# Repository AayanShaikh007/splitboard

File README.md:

# Splitboard
### A split keyboard modelled after the Ergodox with wireless connectivity

## What is the Splitboard?

The splitboard is a diy keyboard modelled after the Ergodox that has wireless bluetooth connectivity and on-board battery charging/management. The most striking thing about the keyboard is probably its distinct appearance compared to other keyboards, but hopefully this will add to the ergonomics of the keyboard. For this keyboard, I wanted to incorporate a number of features that I liked about my last keyboard, such as RGB lighting and Kalih hotswap sockets, while also adressing some of the issues with my last keyboard.

Typical Ergodox layout

## Why did I make the Splitboard?

I made the splitboard as a follow up to my original keyboard to address some mistakes I made in my last keyboard. Firstly, I made the case walls way too thick, at 1 cm, where in reality I only needed 2-4 mm. Additionally, I see now that the keyboard has a very large footprint on my desk and is difficult to move into a comfortable typing position. The splitboard consists of two, very portable halves that can be arranged around your desk in any way you want. Additionally, the case is much more asthetically appealing with low-profile walls (3mm) and a voronoi pattern on the bottom. Check out the product gallery to get a preview of the project.  

# Product Gallery

# BOM Table
| Item                        | Amount | Bought? | Cost (CAD) | Total Cost | Notes                                      | Link |
|-----------------------------|--------|---------|------------|-------------|---------------------------------------------|------|
| Adafruit Feather NRF52840   | 2      | n       | 37.79      | 75.58       |                                             | [AliExpress](https://www.aliexpress.com/item/1005009226053516.html?src=bing&aff_short_key=UneMJZVf&aff_platform=true&isdl=y&albch=shopping&acnt=135105396&albcp=555403205&albag=1301822986926870&slnk=&trgt=pla-2333163674559409&plac=&crea=81363996201255&netw=o&device=c&mtctp=e&utm_source=Bing&utm_medium=shopping&utm_campaign=PA_Bing_CA_PMAX_ALL_maxvalue_20250428_newstore_purchase&utm_content=%E9%87%8D%E5%A4%A7%E4%BB%B6&utm_term=Adafruit%20Feather%20nRF52840%20Express) |
| Switches (need 76)          | 1      | n       | 26.99      | 26.99       |                                             | [Amazon](https://www.amazon.ca/Kailh-Mechanical-Keyboard-Switches-Bronze/dp/B078872V4C) |
| Kalih Sockets               | 1      | n       | 13.57      | 13.57       |                                             | [AliExpress](https://www.aliexpress.com/item/1005007476614771.html) |
| Diodes                      | 1      | n       | 11.36      | 11.36       | Possibly cheaper if bought with other stuff | [AliExpress](https://www.aliexpress.com/item/4000142272546.html) |
| SK6812mini-e                | 1      | n       | 8.04       | 8.04        |                                             | [AliExpress](https://www.aliexpress.com/item/1005009217389452.html) |
| Keycaps                     | 1      | n       | 29.99      | 29.99       |                                             | [Amazon](https://www.amazon.ca/124-Key-Keycaps-Percent-Keyboard-Dye-Sub/dp/B09NRK5B3L) |
| PCB Manufacturing           | 2      | n       | 19.89      | 39.78       | $20 highway coupon (not applied)            | — |
| Stabilizers                 | 1      | n       | 7.29       | 7.29        |                                             | [AliExpress](https://www.aliexpress.com/item/1005009141481219.html) |

|               |        |         |        |         |             |             |
|---------------|--------|---------|--------|---------|-------------|-------------|
|               |        |         | **CAD** | **USD** |             |             |
| **Total Cost**|        |         | 212.60 | 155.20  | Note: 150 USD = 204.58 CAD | |

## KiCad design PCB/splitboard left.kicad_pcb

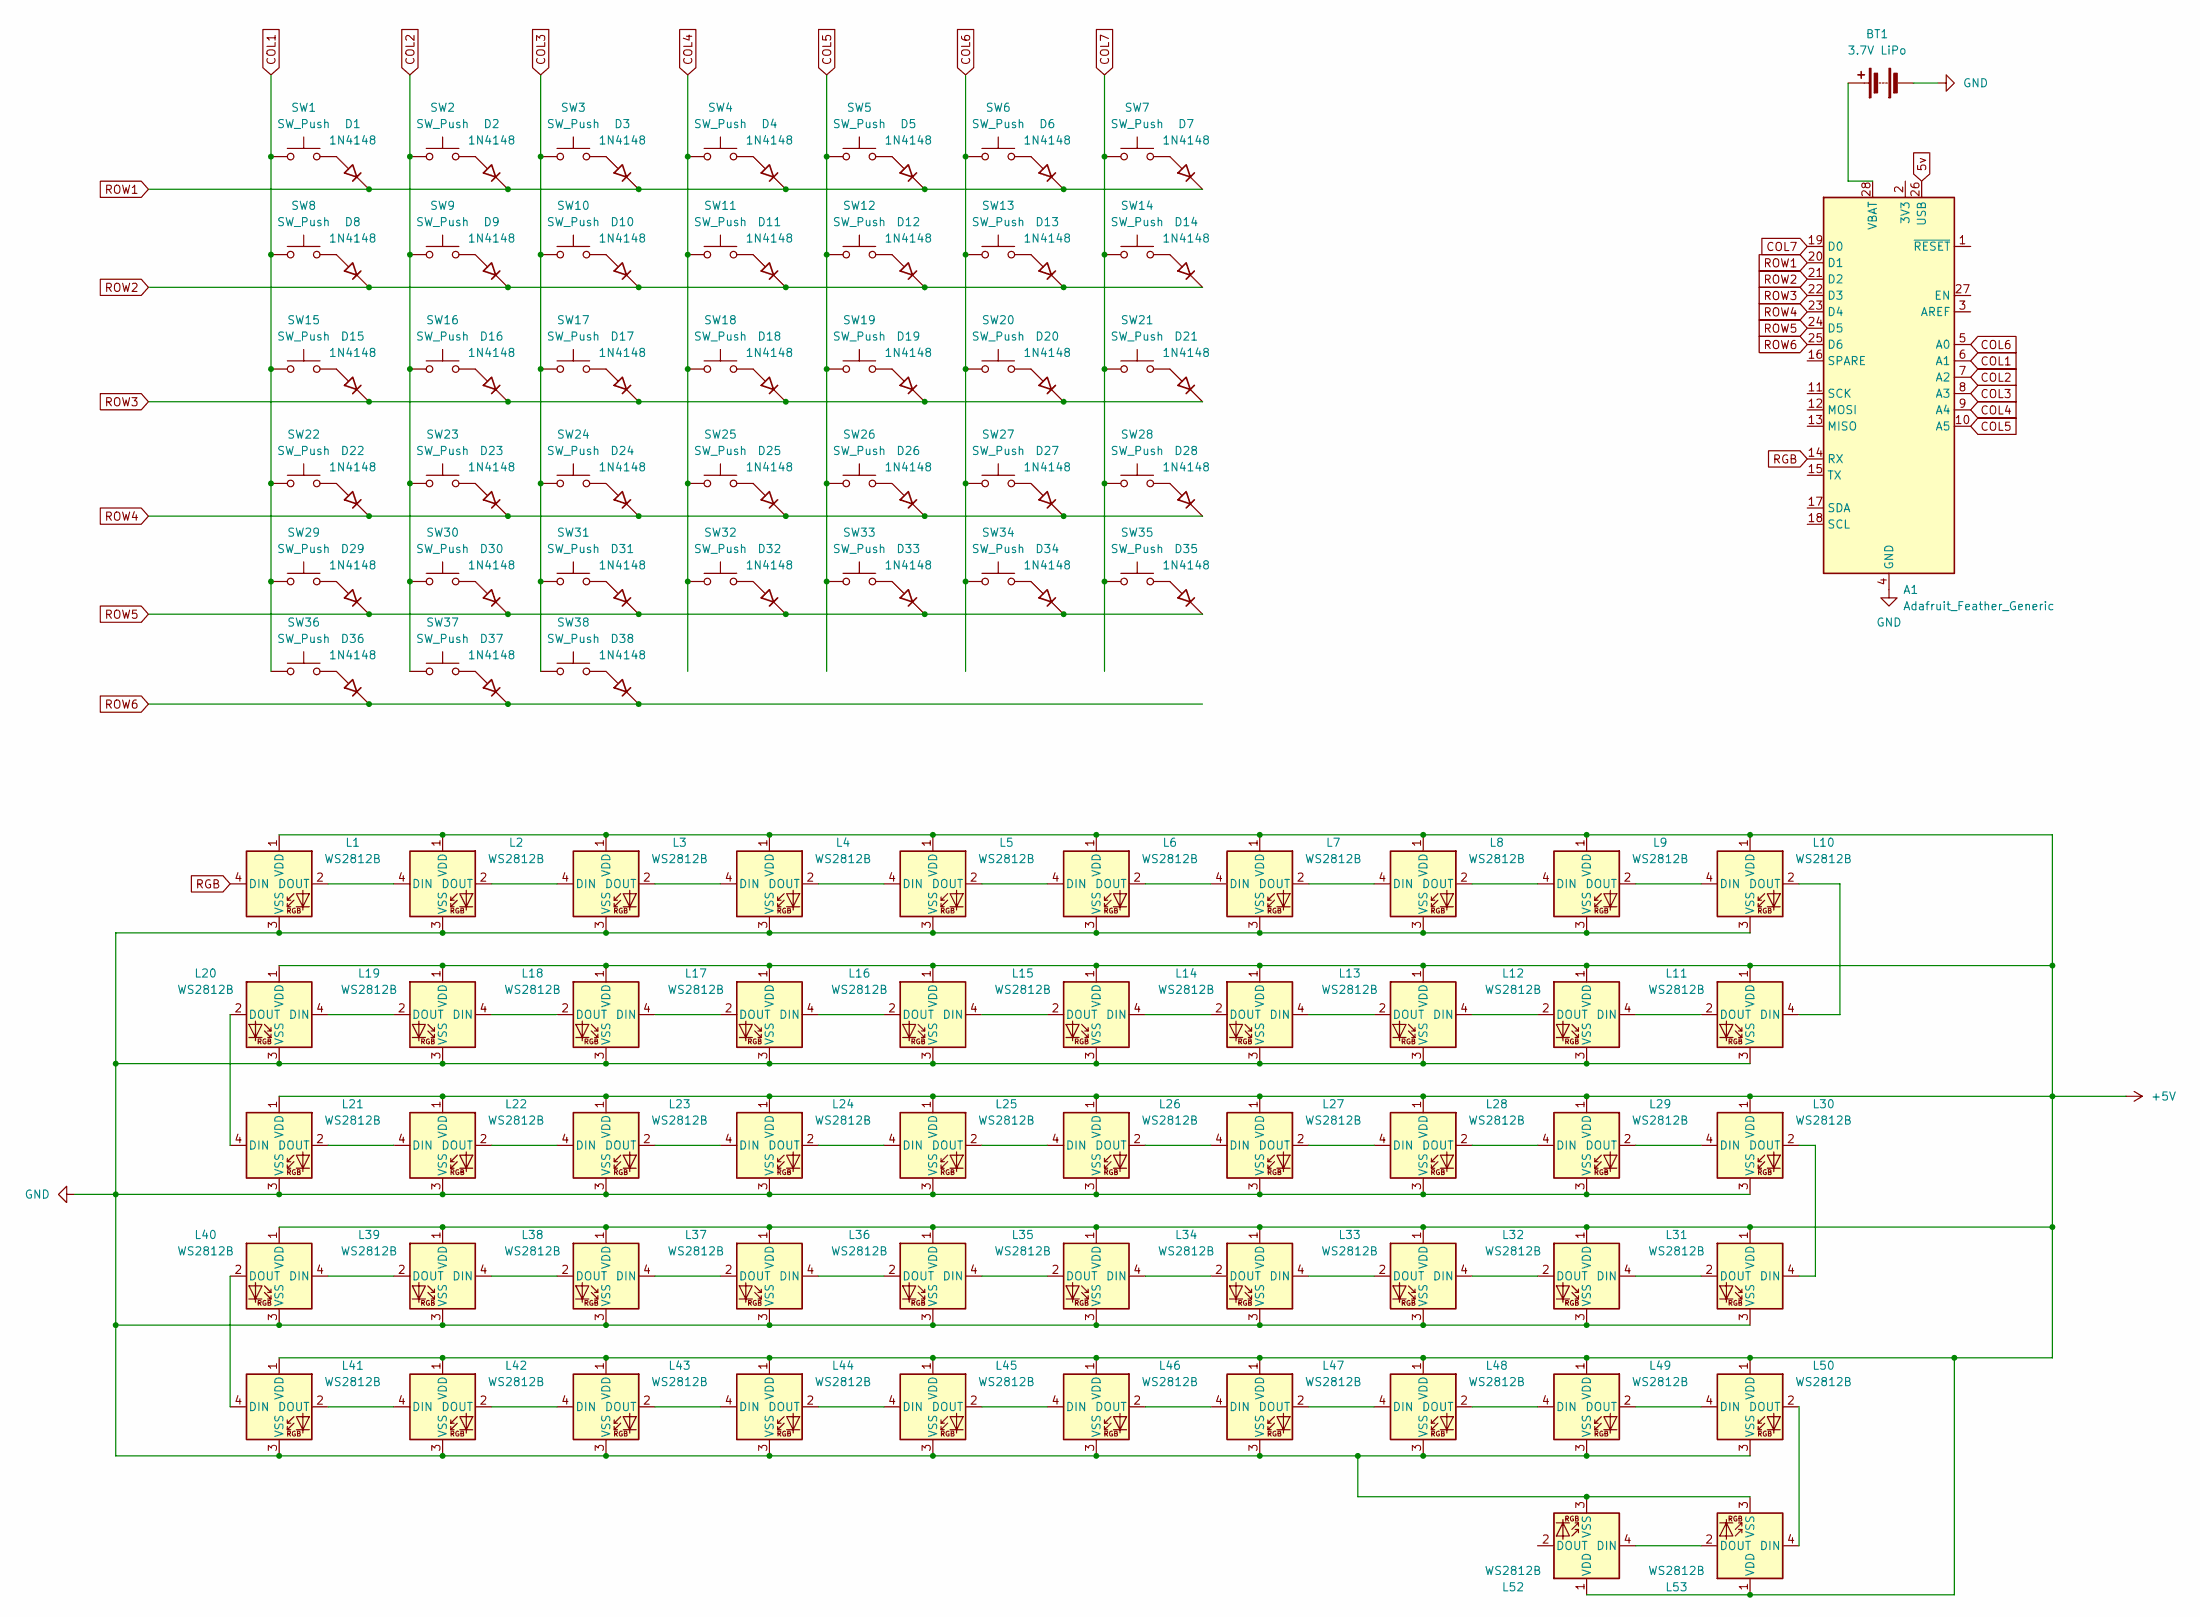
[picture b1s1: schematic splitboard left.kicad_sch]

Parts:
A1: Adafruit_Feather_Generic; Adafruit_Feather
BT1: 3.7V LiPo; JST_PH_S2B-PH-K_1x02_P2.00mm_Horizontal
D1, D2, D3, D4, D5, D6, D7, D8, D9, D10, D11, D12, D13, D14, D15, D16, D17, D18, D19, D20, D21, D22, D23, D24, D25, D26, D27, D28, D29, D30, D31, D32, D33, D34, D35, D36, D37, D38: 1N4148; DO35-7
L1, L2, L3, L4, L5, L6, L7, L8, L9, L10, L11, L12, L13, L14, L15, L16, L17, L18, L19, L20, L21, L22, L23, L24, L25, L26, L27, L28, L29, L30, L31, L32, L33, L34, L35, L36, L37, L38, L39, L40, L41, L42, L43, L44, L45, L46, L47, L48, L49, L50, L52, L53: WS2812B; BAcklight
SW1, SW8, SW15, SW21, SW22: SW_Push; SW_Hotswap_Kailh_MX_1.50u
SW2, SW3, SW4, SW5, SW6, SW7, SW9, SW10, SW11, SW12, SW13, SW16, SW17, SW18, SW19, SW20, SW23, SW24, SW25, SW26, SW27, SW28, SW29, SW30, SW31, SW32, SW33, SW36, SW37, SW38: SW_Push; SW_Hotswap_Kailh_MX_1.00u
SW14: SW_Push; SW_Hotswap_Kailh_MX_1.50u_90deg
SW34, SW35: SW_Push; SW_Hotswap_Kailh_MX_2.00u

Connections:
5v: A1.26 (USB)
+5V: L1.1 (VDD), L2.1 (VDD), L3.1 (VDD), L4.1 (VDD), L5.1 (VDD), L6.1 (VDD), L7.1 (VDD), L8.1 (VDD), L9.1 (VDD), L10.1 (VDD), L11.1 (VDD), L12.1 (VDD), L13.1 (VDD), L14.1 (VDD), L15.1 (VDD), L16.1 (VDD), L17.1 (VDD), L18.1 (VDD), L19.1 (VDD), L20.1 (VDD), L21.1 (VDD), L22.1 (VDD), L23.1 (VDD), L24.1 (VDD), L25.1 (VDD), L26.1 (VDD), L27.1 (VDD), L28.1 (VDD), L29.1 (VDD), L30.1 (VDD), L31.1 (VDD), L32.1 (VDD), L33.1 (VDD), L34.1 (VDD), L35.1 (VDD), L36.1 (VDD), L37.1 (VDD), L38.1 (VDD), L39.1 (VDD), L40.1 (VDD), L41.1 (VDD), L42.1 (VDD), L43.1 (VDD), L44.1 (VDD), L45.1 (VDD), L46.1 (VDD), L47.1 (VDD), L48.1 (VDD), L49.1 (VDD), L50.1 (VDD), L52.1 (VDD), L53.1 (VDD)
COL1: A1.6 (A1), SW1.1, SW8.1, SW15.1, SW22.1, SW29.1, SW36.1
COL2: A1.7 (A2), SW2.1, SW9.1, SW16.1, SW23.1, SW30.1, SW37.1
COL3: A1.8 (A3), SW3.1, SW10.1, SW17.1, SW24.1, SW31.1, SW38.1
COL4: A1.9 (A4), SW4.1, SW11.1, SW18.1, SW25.1, SW32.1
COL5: A1.10 (A5), SW5.1, SW12.1, SW19.1, SW26.1, SW33.1
COL6: A1.5 (A0), SW6.1, SW13.1, SW20.1, SW27.1, SW34.1
COL7: A1.19 (D0), SW7.1, SW14.1, SW21.1, SW28.1, SW35.1
GND: A1.4 (GND), BT1.2 (-), L1.3 (VSS), L2.3 (VSS), L3.3 (VSS), L4.3 (VSS), L5.3 (VSS), L6.3 (VSS), L7.3 (VSS), L8.3 (VSS), L9.3 (VSS), L10.3 (VSS), L11.3 (VSS), L12.3 (VSS), L13.3 (VSS), L14.3 (VSS), L15.3 (VSS), L16.3 (VSS), L17.3 (VSS), L18.3 (VSS), L19.3 (VSS), L20.3 (VSS), L21.3 (VSS), L22.3 (VSS), L23.3 (VSS), L24.3 (VSS), L25.3 (VSS), L26.3 (VSS), L27.3 (VSS), L28.3 (VSS), L29.3 (VSS), L30.3 (VSS), L31.3 (VSS), L32.3 (VSS), L33.3 (VSS), L34.3 (VSS), L35.3 (VSS), L36.3 (VSS), L37.3 (VSS), L38.3 (VSS), L39.3 (VSS), L40.3 (VSS), L41.3 (VSS), L42.3 (VSS), L43.3 (VSS), L44.3 (VSS), L45.3 (VSS), L46.3 (VSS), L47.3 (VSS), L48.3 (VSS), L49.3 (VSS), L50.3 (VSS), L52.3 (VSS), L53.3 (VSS)
unnamed: A1.28 (VBAT), BT1.1 (+)
unnamed: D1.2 (A), SW1.2
unnamed: D2.2 (A), SW2.2
unnamed: D3.2 (A), SW3.2
unnamed: D4.2 (A), SW4.2
unnamed: D5.2 (A), SW5.2
unnamed: D6.2 (A), SW6.2
unnamed: D7.2 (A), SW7.2
unnamed: D8.2 (A), SW8.2
unnamed: D9.2 (A), SW9.2
unnamed: D10.2 (A), SW10.2
unnamed: D11.2 (A), SW11.2
unnamed: D12.2 (A), SW12.2
unnamed: D13.2 (A), SW13.2
unnamed: D14.2 (A), SW14.2
unnamed: D15.2 (A), SW15.2
unnamed: D16.2 (A), SW16.2
unnamed: D17.2 (A), SW17.2
unnamed: D18.2 (A), SW18.2
unnamed: D19.2 (A), SW19.2
unnamed: D20.2 (A), SW20.2
unnamed: D21.2 (A), SW21.2
unnamed: D22.2 (A), SW22.2
unnamed: D23.2 (A), SW23.2
unnamed: D24.2 (A), SW24.2
unnamed: D25.2 (A), SW25.2
unnamed: D26.2 (A), SW26.2
unnamed: D27.2 (A), SW27.2
unnamed: D28.2 (A), SW28.2
unnamed: D29.2 (A), SW29.2
unnamed: D30.2 (A), SW30.2
unnamed: D31.2 (A), SW31.2
unnamed: D32.2 (A), SW32.2
unnamed: D33.2 (A), SW33.2
unnamed: D34.2 (A), SW34.2
unnamed: D35.2 (A), SW35.2
unnamed: D36.2 (A), SW36.2
unnamed: D37.2 (A), SW37.2
unnamed: D38.2 (A), SW38.2
unnamed: L1.2 (DOUT), L2.4 (DIN)
unnamed: L2.2 (DOUT), L3.4 (DIN)
unnamed: L3.2 (DOUT), L4.4 (DIN)
unnamed: L4.2 (DOUT), L5.4 (DIN)
unnamed: L5.2 (DOUT), L6.4 (DIN)
unnamed: L6.2 (DOUT), L7.4 (DIN)
unnamed: L7.2 (DOUT), L8.4 (DIN)
unnamed: L8.2 (DOUT), L9.4 (DIN)
unnamed: L9.2 (DOUT), L10.4 (DIN)
unnamed: L10.2 (DOUT), L11.4 (DIN)
unnamed: L11.2 (DOUT), L12.4 (DIN)
unnamed: L12.2 (DOUT), L13.4 (DIN)
unnamed: L13.2 (DOUT), L14.4 (DIN)
unnamed: L14.2 (DOUT), L15.4 (DIN)
unnamed: L15.2 (DOUT), L16.4 (DIN)
unnamed: L16.2 (DOUT), L17.4 (DIN)
unnamed: L17.2 (DOUT), L18.4 (DIN)
unnamed: L18.2 (DOUT), L19.4 (DIN)
unnamed: L19.2 (DOUT), L20.4 (DIN)
unnamed: L20.2 (DOUT), L21.4 (DIN)
unnamed: L21.2 (DOUT), L22.4 (DIN)
unnamed: L22.2 (DOUT), L23.4 (DIN)
unnamed: L23.2 (DOUT), L24.4 (DIN)
unnamed: L24.2 (DOUT), L25.4 (DIN)
unnamed: L25.2 (DOUT), L26.4 (DIN)
unnamed: L26.2 (DOUT), L27.4 (DIN)
unnamed: L27.2 (DOUT), L28.4 (DIN)
unnamed: L28.2 (DOUT), L29.4 (DIN)
unnamed: L29.2 (DOUT), L30.4 (DIN)
unnamed: L30.2 (DOUT), L31.4 (DIN)
unnamed: L31.2 (DOUT), L32.4 (DIN)
unnamed: L32.2 (DOUT), L33.4 (DIN)
unnamed: L33.2 (DOUT), L34.4 (DIN)
unnamed: L34.2 (DOUT), L35.4 (DIN)
unnamed: L35.2 (DOUT), L36.4 (DIN)
unnamed: L36.2 (DOUT), L37.4 (DIN)
unnamed: L37.2 (DOUT), L38.4 (DIN)
unnamed: L38.2 (DOUT), L39.4 (DIN)
unnamed: L39.2 (DOUT), L40.4 (DIN)
unnamed: L40.2 (DOUT), L41.4 (DIN)
unnamed: L41.2 (DOUT), L42.4 (DIN)
unnamed: L42.2 (DOUT), L43.4 (DIN)
unnamed: L43.2 (DOUT), L44.4 (DIN)
unnamed: L44.2 (DOUT), L45.4 (DIN)
unnamed: L45.2 (DOUT), L46.4 (DIN)
unnamed: L46.2 (DOUT), L47.4 (DIN)
unnamed: L47.2 (DOUT), L48.4 (DIN)
unnamed: L48.2 (DOUT), L49.4 (DIN)
unnamed: L49.2 (DOUT), L50.4 (DIN)
unnamed: L50.2 (DOUT), L53.4 (DIN)
unnamed: L52.4 (DIN), L53.2 (DOUT)
RGB: A1.14 (RX), L1.4 (DIN)
ROW1: A1.20 (D1), D1.1 (K), D2.1 (K), D3.1 (K), D4.1 (K), D5.1 (K), D6.1 (K), D7.1 (K)
ROW2: A1.21 (D2), D8.1 (K), D9.1 (K), D10.1 (K), D11.1 (K), D12.1 (K), D13.1 (K), D14.1 (K)
ROW3: A1.22 (D3), D15.1 (K), D16.1 (K), D17.1 (K), D18.1 (K), D19.1 (K), D20.1 (K), D21.1 (K)
ROW4: A1.23 (D4), D22.1 (K), D23.1 (K), D24.1 (K), D25.1 (K), D26.1 (K), D27.1 (K), D28.1 (K)
ROW5: A1.24 (D5), D29.1 (K), D30.1 (K), D31.1 (K), D32.1 (K), D33.1 (K), D34.1 (K), D35.1 (K)
ROW6: A1.25 (D6), D36.1 (K), D37.1 (K), D38.1 (K)

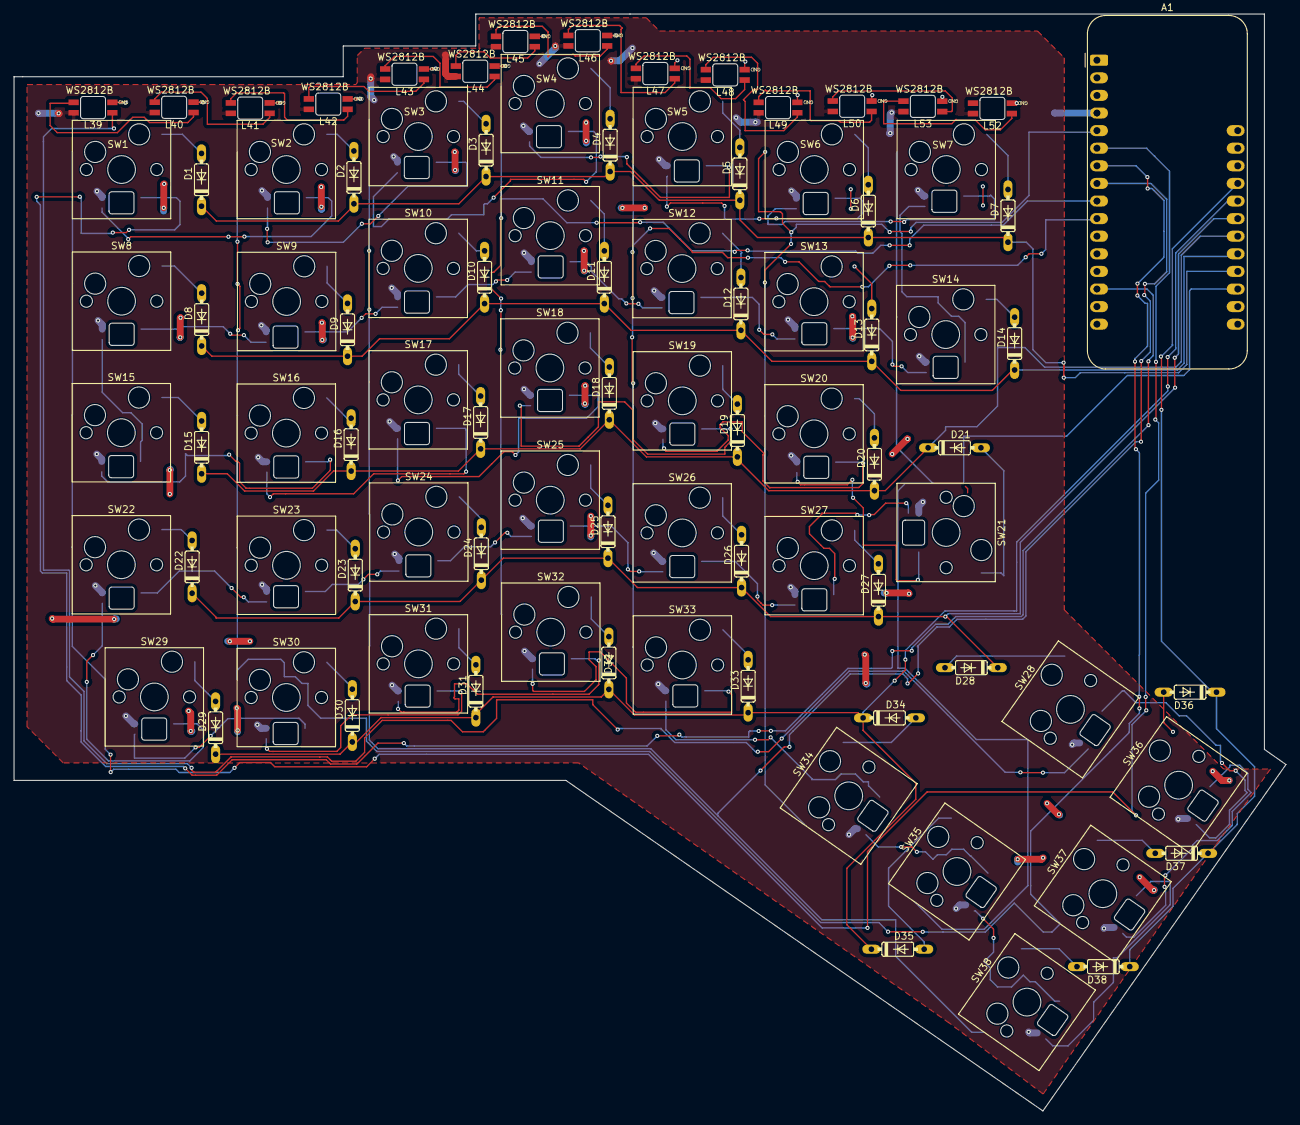
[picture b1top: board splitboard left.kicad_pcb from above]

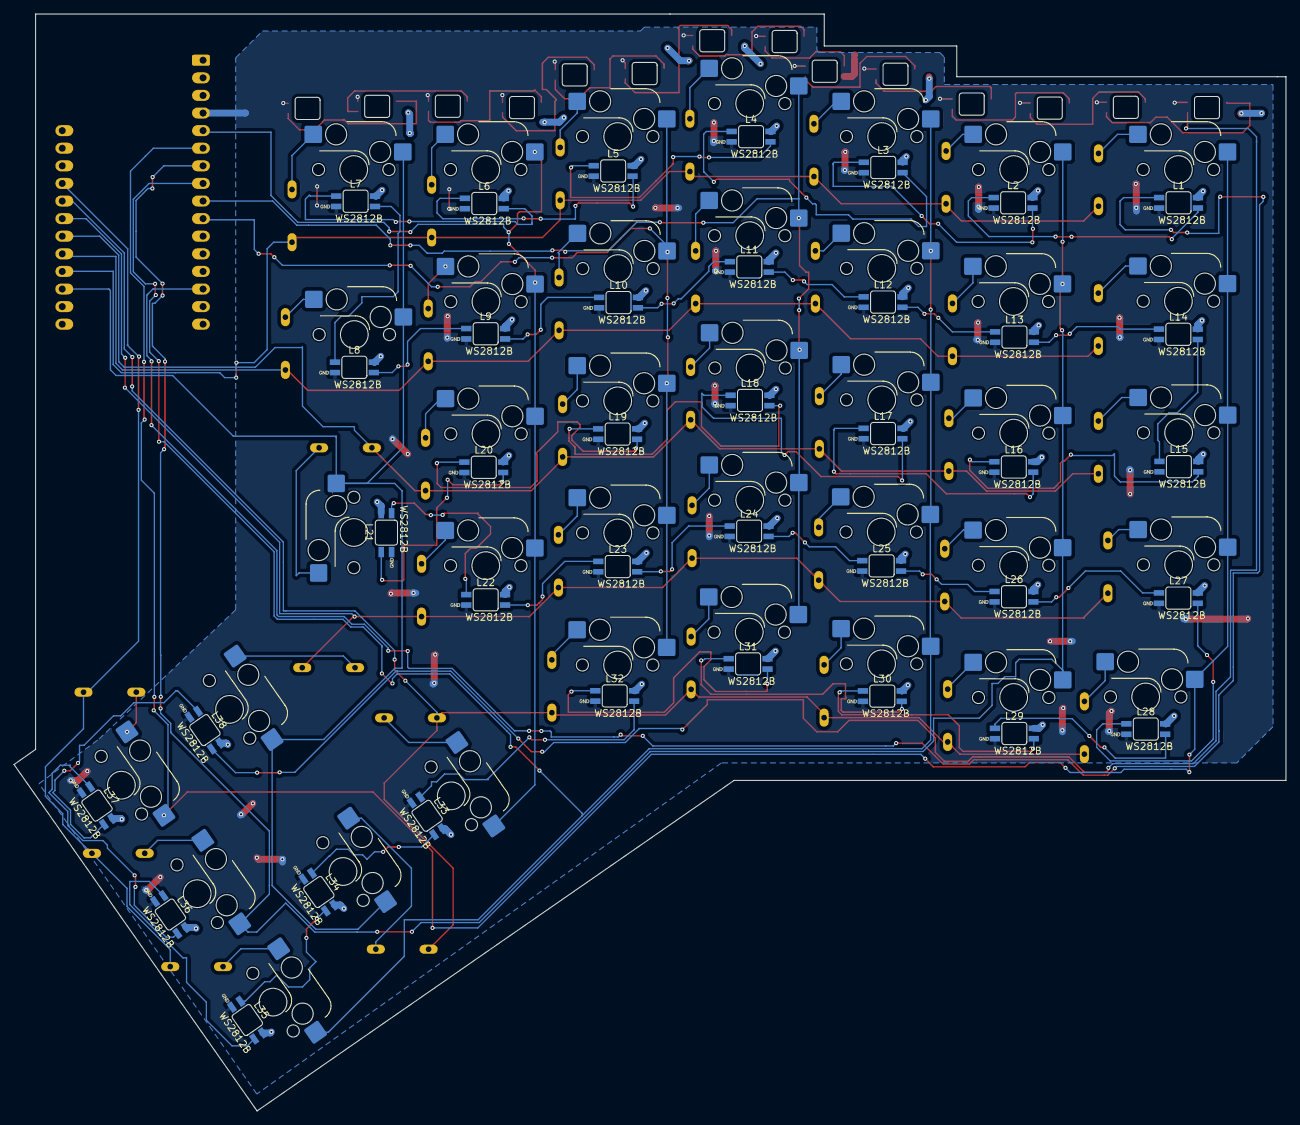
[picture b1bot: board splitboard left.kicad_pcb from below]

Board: 2 copper layers, 183.6 x 158.3 mm, 129 parts (38 on the bottom side), 105 nets.

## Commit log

2025-07-26 final changes
2025-08-04 final commit ???
